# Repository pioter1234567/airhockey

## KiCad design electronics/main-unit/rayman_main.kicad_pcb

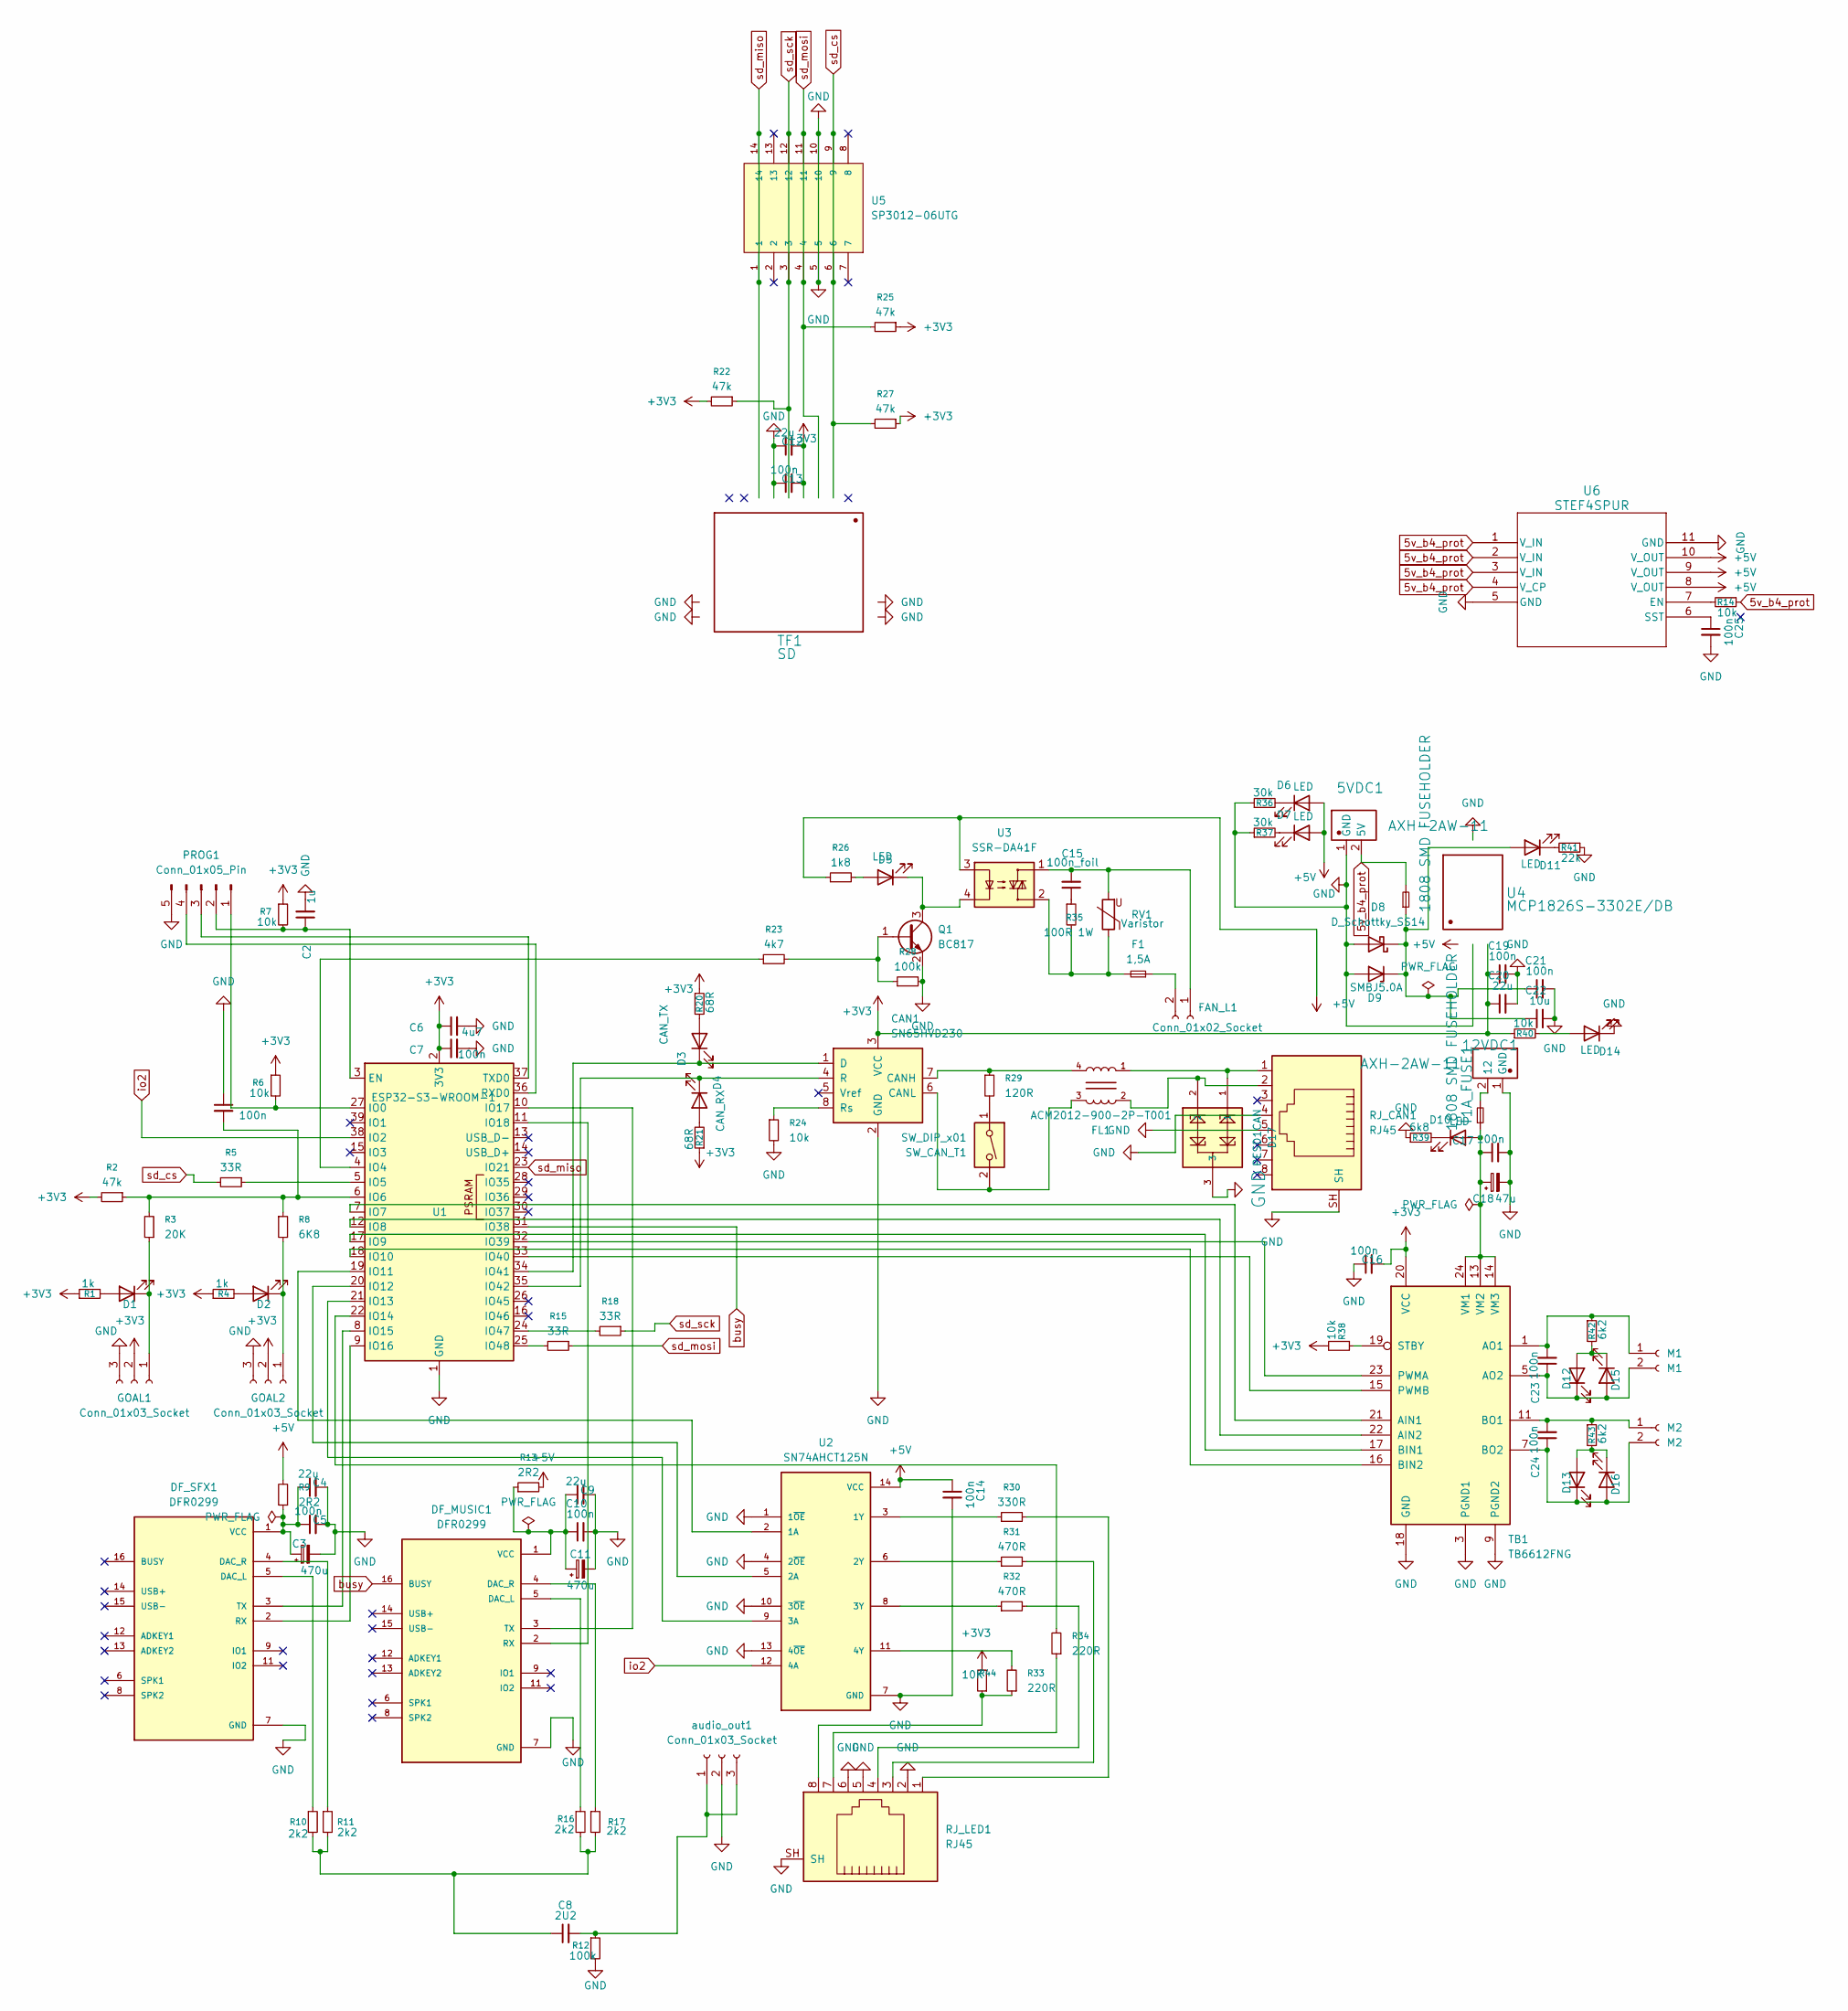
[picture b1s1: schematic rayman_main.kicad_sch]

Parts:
1,0A_FUSE1: 1808 SMD FUSEHOLDER; FUSE_1808; Manufacturer Part 1808 SMD Fuseholder
5VDC1, 12VDC1: AXH-2AW-11; JST_XH_S2B-XH-A-1_1x02_P2.50mm_Horizontal; Manufacturer Part AXH-2AW-11
C1, C5, C7, C10, C13, C14, C16, C17, C19, C21, C23, C24, C25: 100n; C_0805_2012Metric
C2: 1u; C_0805_2012Metric
C3, C11: 470u; CP_Elec_6.3x7.7
C4, C9, C12, C20: 22u; C_0805_2012Metric
C6: 4u7; C_0805_2012Metric
C8: 2U2; C_0805_2012Metric
C15: 100n_foil; C_Rect_L10.0mm_W4.0mm_P7.50mm_FKS3_FKP3
C18: 47u; CP_EIA-7343-31_Kemet-D
C22: 10u; C_0805_2012Metric
CAN1: SN65HVD230; SOIC-8_3.9x4.9mm_P1.27mm
D1, D2, D5, D10, D11, D12, D13, D14, D15, D16: LED; LED_0805_2012Metric
D3: CAN_TX; LED_0805_2012Metric
D4: CAN_RX; LED_0805_2012Metric
D6, D7: LED; LED_0201_0603Metric
D8: D_Schottky_SS14; D_SMA
D9: SMBJ5.0A; D_SMB
D17: PESD1CAN; SOT23-3
DF_MUSIC1: DFR0299; MODULE_DFR0299
DF_SFX1: DFR0299; MODULE_DFR0299
F1: 1,5A; Fuseholder_Cylinder-5x20mm_Schurter_0031_8201_Horizontal_Op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
FAN_L1: Conn_01x02_Socket; TerminalBlock_Phoenix_MKDS-1,5-2_1x02_P5.00mm_Horizontal
FL1: ACM2012-900-2P-T001; FIL_ACM2012-900-2P-T001
GOAL1, GOAL2: Conn_01x03_Socket; JST_XH_B3B-XH-A_1x03_P2.50mm_Vertical
M1: M1; JST_XH_B2B-XH-A_1x02_P2.50mm_Vertical
M2: M2; JST_XH_B2B-XH-A_1x02_P2.50mm_Vertical
PROG1: Conn_01x05_Pin; JST_SH_BM05B-SRSS-TB_1x05-1MP_P1.00mm_Vertical
Q1: BC817; SOT-23
R1, R4: 1k; R_0805_2012Metric
R2, R22, R25, R27: 47k; R_0805_2012Metric
R3: 20K; R_0805_2012Metric
R5, R15, R18: 33R; R_0805_2012Metric
R6, R7, R14, R24, R38, R40: 10k; R_0805_2012Metric
R8: 6K8; R_0805_2012Metric
R9, R13: 2R2; R_0805_2012Metric
R10, R11, R16, R17: 2k2; R_0805_2012Metric
R12, R28: 100k; R_0805_2012Metric
R20, R21: 68R; R_0805_2012Metric
R23: 4k7; R_0805_2012Metric
R26: 1k8; R_0805_2012Metric
R29: 120R; R_0805_2012Metric
R30: 330R; R_0805_2012Metric
R31, R32: 470R; R_0805_2012Metric
R33, R34: 220R; R_0805_2012Metric
R35: 100R 1W; R_2512_6332Metric
R36, R37: 30k; R_0805_2012Metric
R39: 6k8; R_0805_2012Metric
R41: 22k; R_0805_2012Metric
R42, R43: 6k2; R_0805_2012Metric
R44: 10K; R_0805_2012Metric
RJ_CAN1: RJ45; RJ45_Amphenol_RJHSE5380
RJ_LED1: RJ45; RJ45_Amphenol_RJHSE5380
RV1: Varistor; RV_Disc_D16.5mm_W6.7mm_P7.5mm
SW_CAN_T1: SW_DIP_x01; SW_DIP_SPSTx01_Slide_6.7x4.1mm_W7.62mm_P2.54mm_LowProfile
T1A_FUSE1: 1808 SMD FUSEHOLDER; FUSE_1808; Manufacturer Part 1808 SMD Fuseholder
TB1: TB6612FNG; SSOP-24_5.3x8.2mm_P0.65mm
TF1: SD; CUI_MSD-4-A; Manufacturer Part SD
U1: ESP32-S3-WROOM-1
U2: SN74AHCT125N; DIP794W45P254L1930H508Q14; PARTREV Q
U3: SSR-DA41F; Relay_SPST-NO_Fujitsu_FTR-LYAA005x_FormA_Vertical
U4: MCP1826S-3302E/DB; MCP1826S-5002EDB; Manufacturer Part MCP1826S-3302E/DB
U5: SP3012-06UTG; SON50P350X135X55-14N; PARTREV 02/23/17
U6: STEF4SPUR; STEF05PUR
audio_out1: Conn_01x03_Socket; JST_PH_B3B-PH-SM4-TB_1x03-1MP_P2.00mm_Vertical

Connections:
5v_b4_prot: 1,0A_FUSE1.2, 5VDC1.2 (5V), R14.1, U6.1 (V_IN), U6.2 (V_IN), U6.3 (V_IN), U6.4 (V_CP)
+3V3: C6.1, C7.1, C12.2, C13.2, C16.2, C19.1, C20.1, CAN1.3 (VCC), GOAL1.2 (VCC), GOAL2.2 (VCC), R1.1, R2.2, R4.1, R6.1, R7.1, R20.1, R21.1, R22.2, R25.1, R27.1, R38.2, R40.1, R44.2, TB1.20 (VCC), TF1.4 (VDD), U1.2 (3V3), U4.3 (VOUT)
+5V: C14.1, D6.2 (A), D7.2 (A), R9.2, R13.2, R26.1, U2.14 (VCC), U3.3, U4.1 (VIN), U6.8 (V_OUT), U6.9 (V_OUT), U6.10 (V_OUT)
GND: 5VDC1.1 (GND), 12VDC1.1 (GND), C1.1, C2.2, C3.2, C4.2, C5.2, C6.2, C7.2, C9.2, C10.2, C11.2, C12.1, C13.1, C14.2, C16.1, C17.2, C18.2, C19.2, C20.2, C21.2, C22.2, C25.2, CAN1.2 (GND), D8.2 (A), D9.2 (A), D14.1 (K), D17.3, DF_MUSIC1.7 (GND), DF_MUSIC1.10 (GND), DF_SFX1.7 (GND), DF_SFX1.10 (GND), GOAL1.3 (GND), GOAL2.3 (GND), PROG1.5, Q1.2 (E), R12.2, R24.2, R28.2, R36.1, R37.1, R39.1, R41.1, RJ_CAN1.4, RJ_CAN1.5, RJ_CAN1.SH, RJ_LED1.2, RJ_LED1.5, RJ_LED1.6, RJ_LED1.SH, TB1.3 (PGND1), TB1.4 (PGND1), TB1.9 (PGND2), TB1.10 (PGND2), TB1.18 (GND), TF1.6 (VSS), TF1.G1, TF1.G2, TF1.G3, TF1.G4, U1.1 (GND), U1.40 (GND), U1.41 (GND), U2.1 (1~OE), U2.4 (2~OE), U2.7 (GND), U2.10 (3~OE), U2.13 (4~OE), U4.2 (GND), U4.4 (GND), U5.5, U5.10, U6.5 (GND), U6.11 (GND), audio_out1.2 (VCC)
unnamed: 12VDC1.2 (12), T1A_FUSE1.2
unnamed: C8.1, R10.2, R11.2, R16.2, R17.2
unnamed: C15.1, R35.1
unnamed: CAN1.7 (CANH), FL1.4, R29.1
unnamed: CAN1.6 (CANL), FL1.3, SW_CAN_T1.2
unnamed: CAN1.1 (D), D3.1 (K), U1.34 (IO41)
unnamed: CAN1.4 (R), D4.1 (K), U1.35 (IO42)
unnamed: CAN1.8 (Rs), R24.1
unnamed: D1.2 (A), R1.2
unnamed: D1.1 (K), GOAL1.1 (DO), R3.1
unnamed: D2.2 (A), R4.2
unnamed: D2.1 (K), GOAL2.1 (DO), R8.2
unnamed: D3.2 (A), R20.2
unnamed: D4.2 (A), R21.2
unnamed: D5.2 (A), R26.2
unnamed: D5.1 (K), Q1.3 (C), U3.4
unnamed: D6.1 (K), R36.2
unnamed: D7.1 (K), R37.2
unnamed: C17.1, C18.1, D10.2 (A), T1A_FUSE1.1, TB1.13 (VM2), TB1.14 (VM3), TB1.24 (VM1)
unnamed: D10.1 (K), R39.2
unnamed: 1,0A_FUSE1.1, C21.1, C22.1, D8.1 (K), D9.1 (K), D11.2 (A)
unnamed: D11.1 (K), R41.2
unnamed: D12.2 (A), D15.1 (K), R42.2
unnamed: C23.1, D12.1 (K), D15.2 (A), M1.2, TB1.5 (AO2), TB1.6 (AO2)
unnamed: D13.2 (A), D16.1 (K), R43.2
unnamed: C24.1, D13.1 (K), D16.2 (A), M2.2, TB1.7 (BO2), TB1.8 (BO2)
unnamed: D14.2 (A), R40.2
unnamed: D17.1, FL1.1, RJ_CAN1.1
unnamed: D17.2, FL1.2, RJ_CAN1.2
unnamed: DF_MUSIC1.5 (DAC_L), R16.1
unnamed: DF_MUSIC1.4 (DAC_R), R17.1
unnamed: DF_MUSIC1.2 (RX), U1.11 (IO18)
unnamed: DF_MUSIC1.3 (TX), U1.10 (IO17)
unnamed: C9.1, C10.1, C11.1, DF_MUSIC1.1 (VCC), R13.1
unnamed: DF_SFX1.5 (DAC_L), R10.1
unnamed: DF_SFX1.4 (DAC_R), R11.1
unnamed: DF_SFX1.2 (RX), U1.9 (IO16)
unnamed: DF_SFX1.3 (TX), U1.8 (IO15)
unnamed: C3.1, C4.1, C5.1, DF_SFX1.1 (VCC), R9.1
unnamed: F1.2, R35.2, RV1.1, U3.2
unnamed: C15.2, FAN_L1.1, RV1.2, U3.1
unnamed: F1.1, FAN_L1.2
unnamed: C23.2, M1.1, R42.1, TB1.1 (AO1), TB1.2 (AO1)
unnamed: C24.2, M2.1, R43.1, TB1.11 (BO1), TB1.12 (BO1)
unnamed: PROG1.1, R6.2, U1.27 (IO0)
unnamed: C2.1, PROG1.2, R7.2, U1.3 (EN)
unnamed: PROG1.3, U1.37 (TXD0)
unnamed: PROG1.4, U1.36 (RXD0)
unnamed: Q1.1 (B), R23.2, R28.1
unnamed: R29.2, SW_CAN_T1.1
unnamed: R30.2, RJ_LED1.1
unnamed: R31.2, RJ_LED1.3
unnamed: R32.2, RJ_LED1.4
unnamed: R33.1, R44.1, RJ_LED1.8
unnamed: R34.1, RJ_LED1.7
unnamed: TB1.21 (AIN1), U1.7 (IO7)
unnamed: TB1.22 (AIN2), U1.12 (IO8)
unnamed: TB1.17 (BIN1), U1.17 (IO9)
unnamed: TB1.16 (BIN2), U1.18 (IO10)
unnamed: TB1.23 (PWMA), U1.32 (IO39)
unnamed: TB1.15 (PWMB), U1.33 (IO40)
unnamed: R38.1, TB1.19 (STBY)
unnamed: R23.1, U1.4 (IO4)
unnamed: R5.1, U1.5 (IO5)
unnamed: C1.2, R2.1, R3.2, R8.1, U1.6 (IO6)
unnamed: U1.19 (IO11), U2.2 (1A)
unnamed: U1.20 (IO12), U2.5 (2A)
unnamed: U1.21 (IO13), U2.9 (3A)
unnamed: R34.2, U1.22 (IO14)
unnamed: R18.2, U1.24 (IO47)
unnamed: R15.2, U1.25 (IO48)
unnamed: R30.1, U2.3 (1Y)
unnamed: R31.1, U2.6 (2Y)
unnamed: R32.1, U2.8 (3Y)
unnamed: R33.2, U2.11 (4Y)
unnamed: R14.2, U6.7 (EN)
unnamed: C25.1, U6.6 (SST)
unnamed: C8.2, R12.1, audio_out1.1 (DO), audio_out1.3 (GND)
busy: DF_MUSIC1.16 (BUSY), U1.31 (IO38)
io2: U1.38 (IO2), U2.12 (4A)
sd_cs: R5.2, R27.2, TF1.2 (CD/DAT3), U5.6, U5.9
sd_miso: TF1.7 (DAT0), U1.23 (IO21), U5.1, U5.14
sd_mosi: R15.1, R25.2, TF1.3 (CMD), U5.4, U5.11
sd_sck: R18.1, R22.1, TF1.5 (CLK), U5.3, U5.12

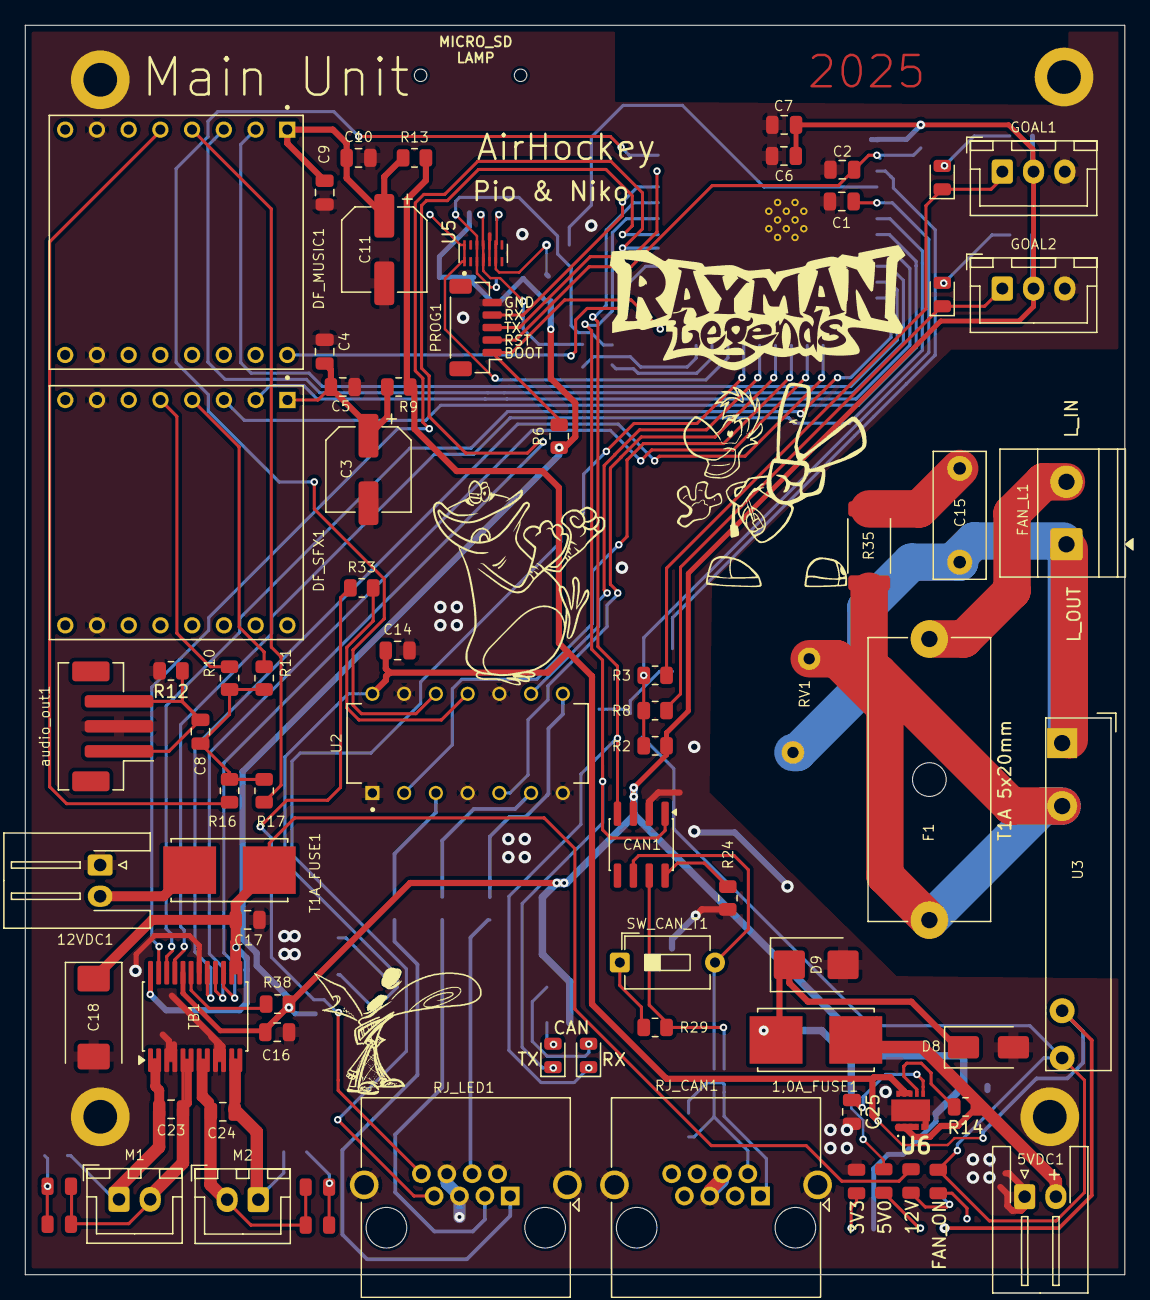
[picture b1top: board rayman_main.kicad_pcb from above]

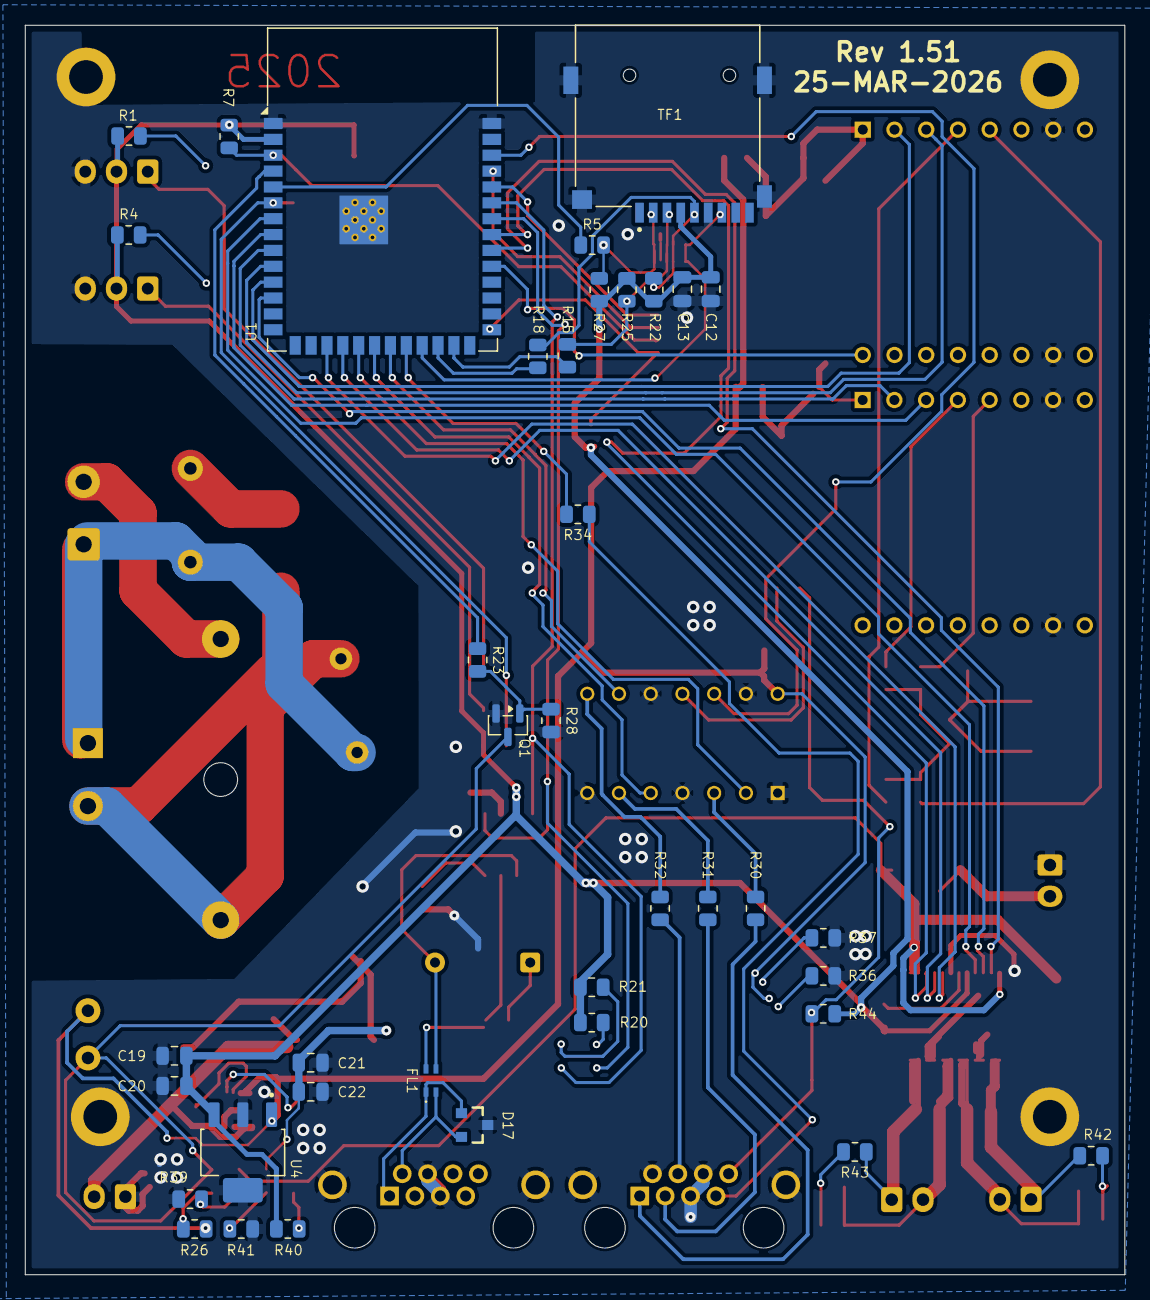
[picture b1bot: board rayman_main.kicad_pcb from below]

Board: 2 copper layers, 88.0 x 100.0 mm, 114 parts (38 on the bottom side), 88 nets.

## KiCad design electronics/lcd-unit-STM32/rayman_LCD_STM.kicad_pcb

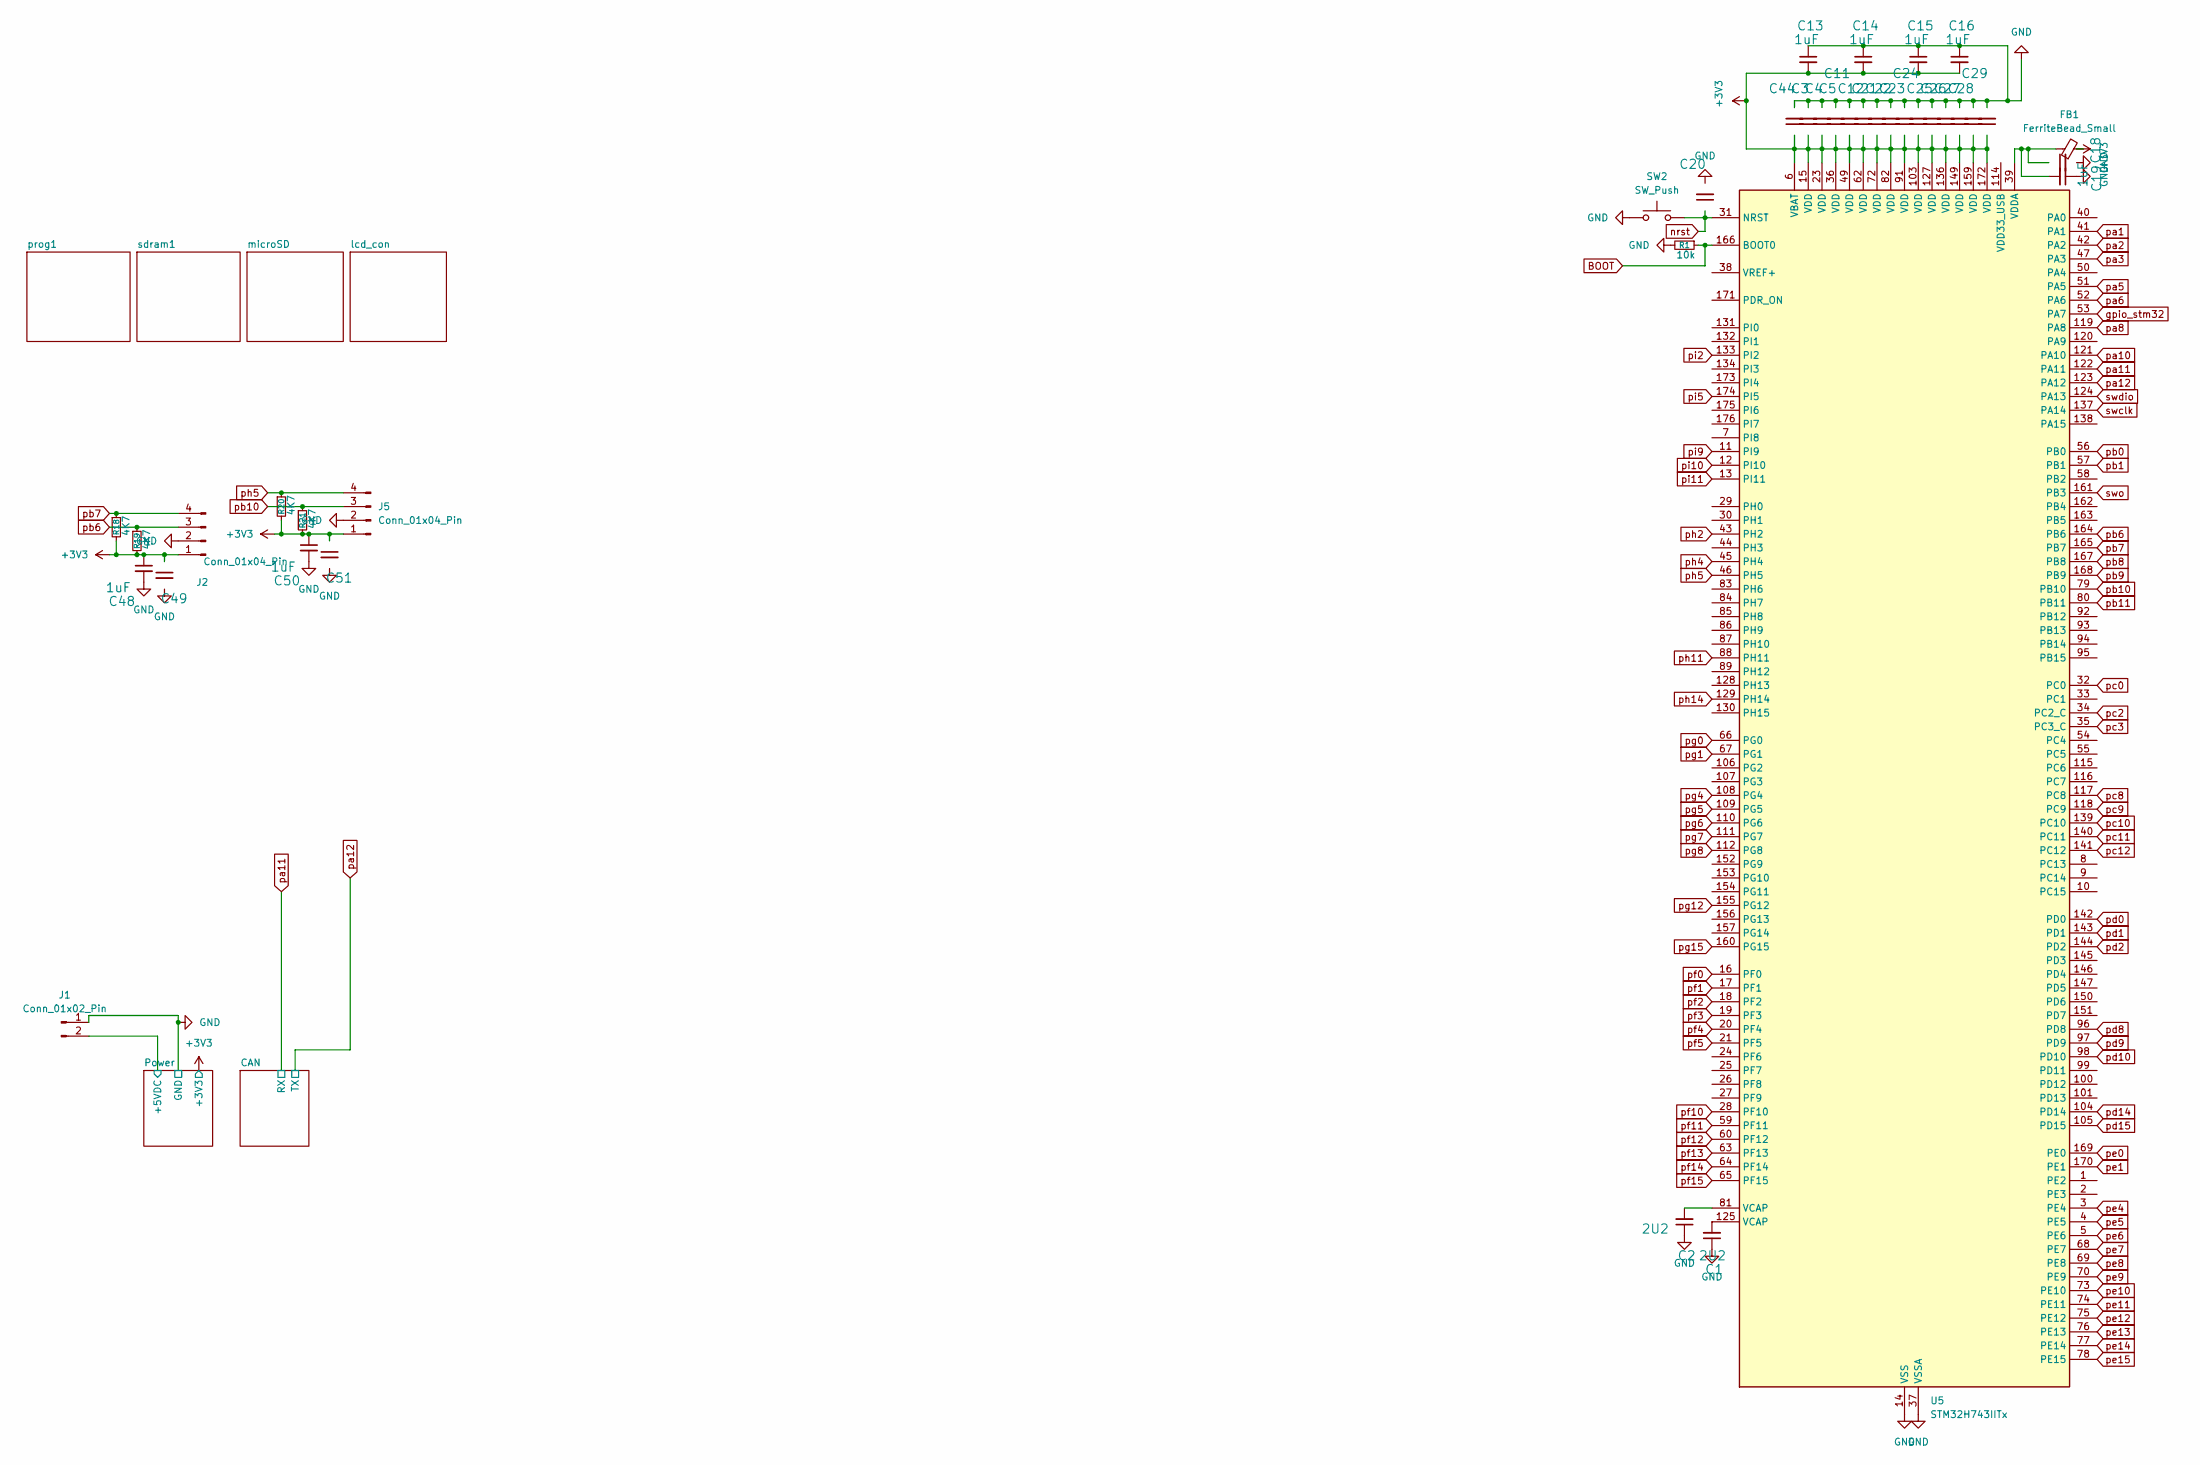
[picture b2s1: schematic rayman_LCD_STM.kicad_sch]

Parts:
C1, C2: 2U2; C_0603_1608Metric; Manufacturer Part 0805ZD106KAT2A
C3, C4, C5, C11, C12, C18, C20, C21, C22, C23, C24, C25, C26, C27, C28, C29, C44, C49, C51: 100nF; C_0603_1608Metric; Manufacturer Part 0805B104K160CT-C
C13, C14, C15, C16, C19, C48, C50: 1uF; C_0603_1608Metric; Manufacturer Part 0805ZD106KAT2A
FB1: FerriteBead_Small; ferrit_0805
J1: Conn_01x02_Pin; Molex_Micro-Latch_53253-0270_1x02_P2.00mm_Vertical
J2, J5: Conn_01x04_Pin; Molex_KK-254_AE-6410-04A_1x04_P2.54mm_Vertical
R1: 10k; R_0805_2012Metric
R18, R19, R20, R21: 4K7; R_0805_2012Metric
SW2: SW_Push; switch tacticle 3_4_2 smd
U5: STM32H743IITx; LQFP-176_24x24mm_P0.5mm

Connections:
+3V3: C3.1, C4.1, C5.1, C11.1, C12.1, C13.2, C14.2, C15.2, C16.2, C21.1, C22.1, C23.1, C24.1, C25.1, C26.1, C27.1, C28.1, C29.1, C44.1, C48.1, C49.1, C50.1, C51.1, FB1.2, J2.1 (VCC), J5.1 (VCC), R18.2, R19.2, R20.2, R21.2, U5.6 (VBAT), U5.15 (VDD), U5.23 (VDD), U5.36 (VDD), U5.49 (VDD), U5.62 (VDD), U5.72 (VDD), U5.82 (VDD), U5.91 (VDD), U5.103 (VDD), U5.127 (VDD), U5.136 (VDD), U5.149 (VDD), U5.159 (VDD), U5.172 (VDD); also elsewhere on the board
/Power/+5VDC: J1.2; also elsewhere on the board
BOOT: R1.1, U5.166 (BOOT0); also elsewhere on the board
GND: C1.1, C2.1, C3.2, C4.2, C5.2, C11.2, C12.2, C13.1, C14.1, C15.1, C16.1, C18.2, C19.1, C20.2, C21.2, C22.2, C23.2, C24.2, C25.2, C26.2, C27.2, C28.2, C29.2, C44.2, C48.2, C49.2, C50.2, C51.2, J1.1, J2.2 (GND), J5.2 (GND), R1.2, SW2.1, U5.14 (VSS), U5.22 (VSS), U5.37 (VSSA), U5.48 (VSS), U5.61 (VSS), U5.71 (VSS), U5.90 (VSS), U5.102 (VSS), U5.113 (VSS), U5.126 (VSS), U5.135 (VSS), U5.148 (VSS), U5.158 (VSS); also elsewhere on the board
unnamed: C1.2, U5.125 (VCAP)
unnamed: C2.2, U5.81 (VCAP)
unnamed: C18.1, C19.2, FB1.1, U5.39 (VDDA)
gpio_stm32: U5.53 (PA7); also elsewhere on the board
nrst: C20.1, SW2.2, U5.31 (NRST); also elsewhere on the board
pa1: U5.41 (PA1); also elsewhere on the board
pa2: U5.42 (PA2); also elsewhere on the board
pa3: U5.47 (PA3); also elsewhere on the board
pa5: U5.51 (PA5); also elsewhere on the board
pa6: U5.52 (PA6); also elsewhere on the board
pa8: U5.119 (PA8); also elsewhere on the board
pa10: U5.121 (PA10); also elsewhere on the board
pa11: U5.122 (PA11); also elsewhere on the board
pa12: U5.123 (PA12); also elsewhere on the board
pb0: U5.56 (PB0); also elsewhere on the board
pb1: U5.57 (PB1); also elsewhere on the board
pb6: J2.3 (SCK), R19.1, U5.164 (PB6)
pb7: J2.4 (SDK), R18.1, U5.165 (PB7)
pb8: U5.167 (PB8); also elsewhere on the board
pb9: U5.168 (PB9); also elsewhere on the board
pb10: J5.3 (SCK), R21.1, U5.79 (PB10)
pb11: U5.80 (PB11); also elsewhere on the board
pc0: U5.32 (PC0); also elsewhere on the board
pc2: U5.34 (PC2_C); also elsewhere on the board
pc3: U5.35 (PC3_C); also elsewhere on the board
pc8: U5.117 (PC8); also elsewhere on the board
pc9: U5.118 (PC9); also elsewhere on the board
pc10: U5.139 (PC10); also elsewhere on the board
pc11: U5.140 (PC11); also elsewhere on the board
pc12: U5.141 (PC12); also elsewhere on the board
pd0: U5.142 (PD0); also elsewhere on the board
pd1: U5.143 (PD1); also elsewhere on the board
pd2: U5.144 (PD2); also elsewhere on the board
pd8: U5.96 (PD8); also elsewhere on the board
pd9: U5.97 (PD9); also elsewhere on the board
pd10: U5.98 (PD10); also elsewhere on the board
pd14: U5.104 (PD14); also elsewhere on the board
pd15: U5.105 (PD15); also elsewhere on the board
pe0: U5.169 (PE0); also elsewhere on the board
pe1: U5.170 (PE1); also elsewhere on the board
pe4: U5.3 (PE4); also elsewhere on the board
pe5: U5.4 (PE5); also elsewhere on the board
pe6: U5.5 (PE6); also elsewhere on the board
pe7: U5.68 (PE7); also elsewhere on the board
pe8: U5.69 (PE8); also elsewhere on the board
pe9: U5.70 (PE9); also elsewhere on the board
pe10: U5.73 (PE10); also elsewhere on the board
pe11: U5.74 (PE11); also elsewhere on the board
pe12: U5.75 (PE12); also elsewhere on the board
pe13: U5.76 (PE13); also elsewhere on the board
pe14: U5.77 (PE14); also elsewhere on the board
pe15: U5.78 (PE15); also elsewhere on the board
pf0: U5.16 (PF0); also elsewhere on the board
pf1: U5.17 (PF1); also elsewhere on the board
pf2: U5.18 (PF2); also elsewhere on the board
pf3: U5.19 (PF3); also elsewhere on the board
pf4: U5.20 (PF4); also elsewhere on the board
pf5: U5.21 (PF5); also elsewhere on the board
pf10: U5.28 (PF10); also elsewhere on the board
pf11: U5.59 (PF11); also elsewhere on the board
pf12: U5.60 (PF12); also elsewhere on the board
pf13: U5.63 (PF13); also elsewhere on the board
pf14: U5.64 (PF14); also elsewhere on the board
pf15: U5.65 (PF15); also elsewhere on the board
pg0: U5.66 (PG0); also elsewhere on the board
pg1: U5.67 (PG1); also elsewhere on the board
pg4: U5.108 (PG4); also elsewhere on the board
pg5: U5.109 (PG5); also elsewhere on the board
pg6: U5.110 (PG6); also elsewhere on the board
pg7: U5.111 (PG7); also elsewhere on the board
pg8: U5.112 (PG8); also elsewhere on the board
pg12: U5.155 (PG12); also elsewhere on the board
pg15: U5.160 (PG15); also elsewhere on the board
ph2: U5.43 (PH2); also elsewhere on the board
ph4: U5.45 (PH4); also elsewhere on the board
ph5: J5.4 (SDK), R20.1, U5.46 (PH5)
ph11: U5.88 (PH11); also elsewhere on the board
ph14: U5.129 (PH14); also elsewhere on the board
pi2: U5.133 (PI2); also elsewhere on the board
pi5: U5.174 (PI5); also elsewhere on the board
pi9: U5.11 (PI9); also elsewhere on the board
pi10: U5.12 (PI10); also elsewhere on the board
pi11: U5.13 (PI11); also elsewhere on the board
swclk: U5.137 (PA14); also elsewhere on the board
swdio: U5.124 (PA13); also elsewhere on the board
swo: U5.161 (PB3); also elsewhere on the board

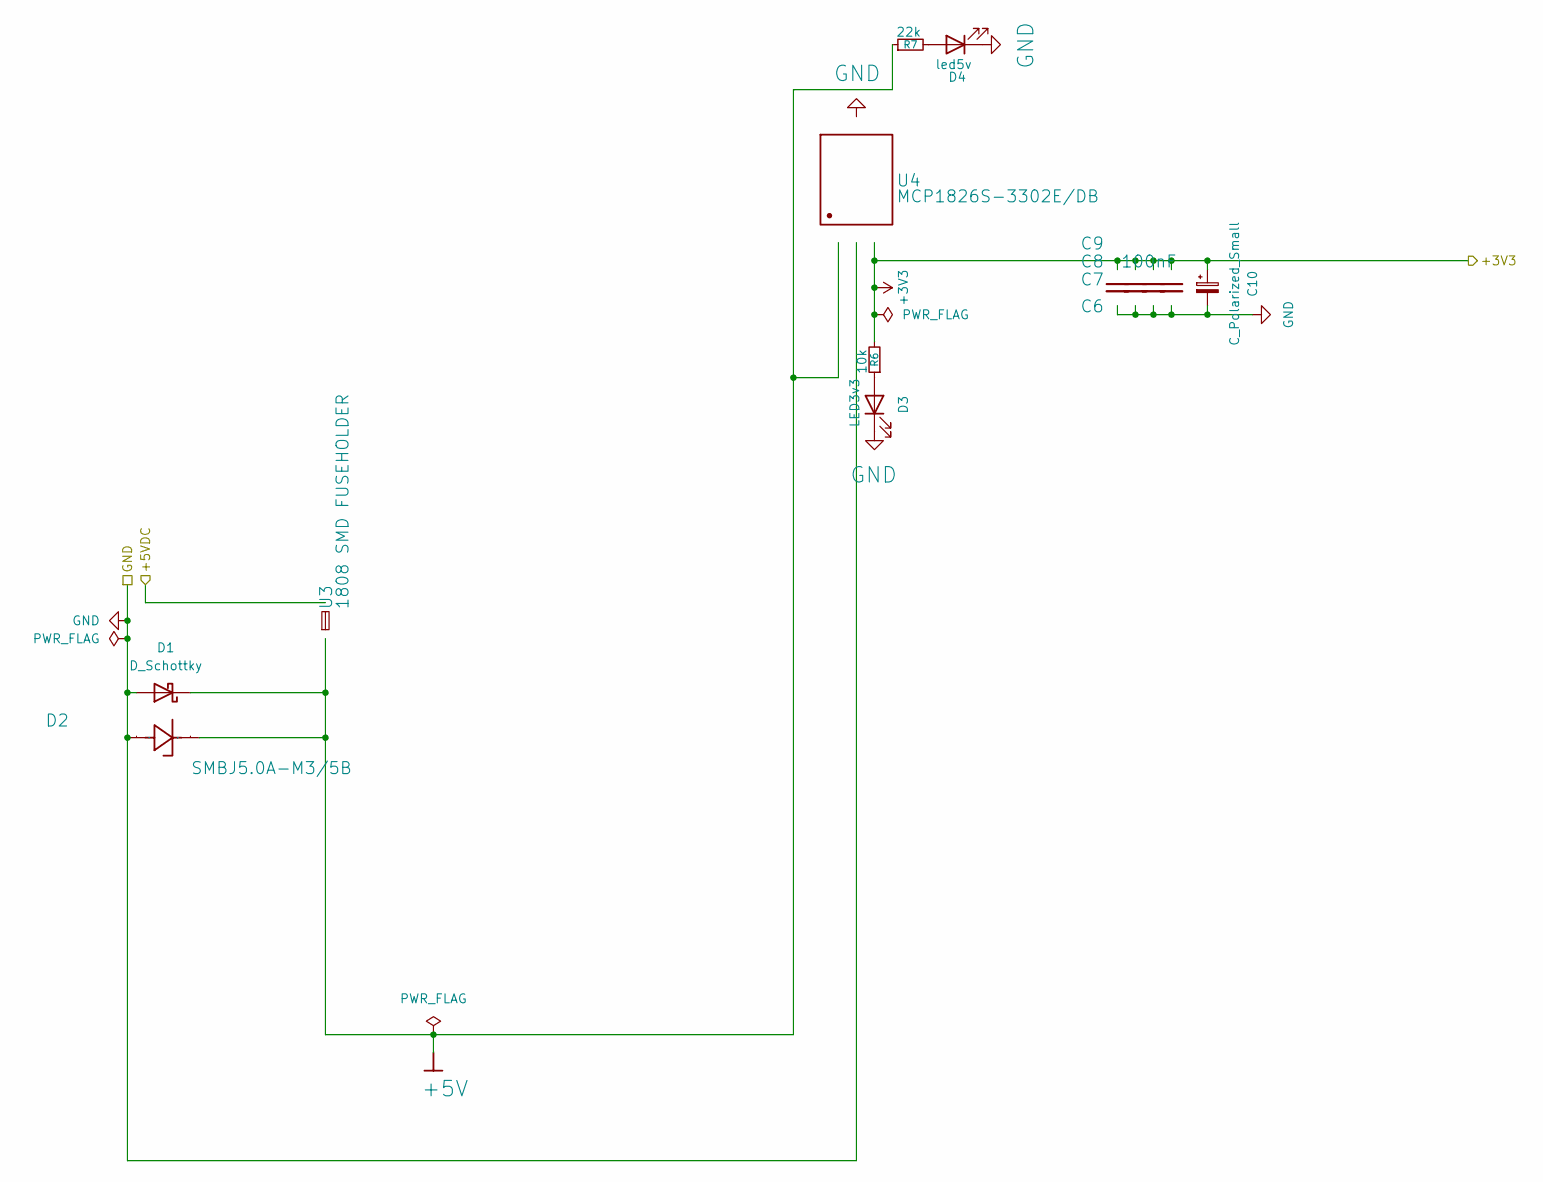
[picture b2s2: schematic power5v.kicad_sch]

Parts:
C6, C7, C8, C9: 100nF; C_0603_1608Metric; Manufacturer Part 0805B104K160CT-C
C10: C_Polarized_Small; CP_7343-tantal
D1: D_Schottky; D_SMA
D2: SMBJ5.0A-M3/5B; D_SMB; Manufacturer Part SMBJ5.0A-M3/5B
D3: LED3v3; LED_0805_2012Metric
D4: led5v; LED_0805_2012Metric
R6: 10k; R_0805_2012Metric
R7: 22k; R_0805_2012Metric
U3: 1808 SMD FUSEHOLDER; FUSE_1808; Manufacturer Part 1808 SMD Fuseholder
U4: MCP1826S-3302E/DB; MCP1826S-5002EDB; Manufacturer Part MCP1826S-3302E/DB

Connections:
+3V3: C6.1, C7.1, C8.1, C9.1, C10.1, R6.2, U4.3 (VOUT); also elsewhere on the board
+5V: D1.1 (K), D2.1 (K), R7.1, U3.1, U4.1 (VIN)
/Power/+5VDC: U3.2; also elsewhere on the board
GND: C6.2, C7.2, C8.2, C9.2, C10.2, D1.2 (A), D2.2 (A), D3.1 (K), D4.1 (K), U4.2 (GND), U4.4 (GND); also elsewhere on the board
unnamed: D3.2 (A), R6.1
unnamed: D4.2 (A), R7.2

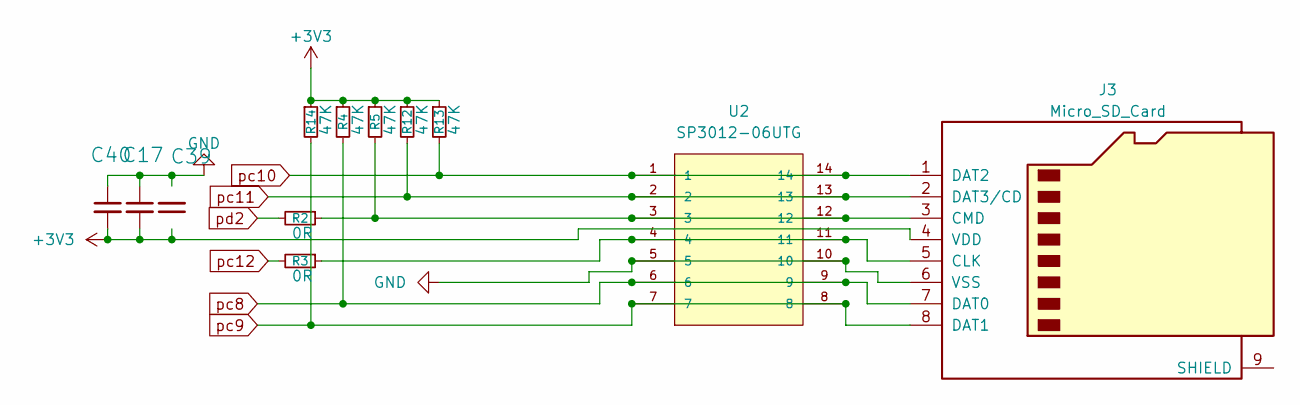
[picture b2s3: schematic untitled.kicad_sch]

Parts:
C17: 1uF; C_0603_1608Metric; Manufacturer Part 0805ZD106KAT2A
C39: 100nF; C_0603_1608Metric; Manufacturer Part 0805B104K160CT-C
C40: 10uF; C_0603_1608Metric; Manufacturer Part 0805ZD106KAT2A
J3: Micro_SD_Card; CUI_MSD-4-A
R2, R3: 0R; R_0805_2012Metric
R4, R5, R12, R13, R14: 47K; R_0805_2012Metric
U2: SP3012-06UTG; SON50P350X135X55-14N; PARTREV 02/23/17

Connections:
+3V3: C17.2, C39.1, C40.2, J3.4 (VDD), R4.1, R5.1, R12.1, R13.1, R14.1; also elsewhere on the board
GND: C17.1, C39.2, C40.1, J3.6 (VSS), U2.5, U2.10; also elsewhere on the board
unnamed: J3.5 (CLK), R3.1, U2.4, U2.11
unnamed: J3.3 (CMD), R2.1, R5.2, U2.3, U2.12
pc8: J3.7 (DAT0), R4.2, U2.6, U2.9; also elsewhere on the board
pc9: J3.8 (DAT1), R14.2, U2.7, U2.8; also elsewhere on the board
pc10: J3.1 (DAT2), R13.2, U2.1, U2.14; also elsewhere on the board
pc11: J3.2 (DAT3/CD), R12.2, U2.2, U2.13; also elsewhere on the board
pc12: R3.2; also elsewhere on the board
pd2: R2.2; also elsewhere on the board

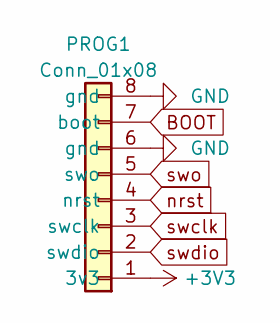
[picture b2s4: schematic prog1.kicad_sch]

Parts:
PROG1: Conn_01x08; Hirose_FH12-8S-0.5SH_1x08-1MP_P0.50mm_Horizontal

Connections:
+3V3: PROG1.1 (3v3); also elsewhere on the board
BOOT: PROG1.7 (boot); also elsewhere on the board
GND: PROG1.6 (gnd), PROG1.8 (gnd); also elsewhere on the board
nrst: PROG1.4 (nrst); also elsewhere on the board
swclk: PROG1.3 (swclk); also elsewhere on the board
swdio: PROG1.2 (swdio); also elsewhere on the board
swo: PROG1.5 (swo); also elsewhere on the board
